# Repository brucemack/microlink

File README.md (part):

# Overview

Is it possible to build a full EchoLink&reg; node using a $6 microcontroller?  I'm not completely sure, but
let's find out. The goal of this project is to create the smallest, 
cheapest way to put a radio onto the EchoLink network. If you are new 
to the world of EchoLink please 
[see the official website](https://www.echolink.org/) for complete information. EchoLink is a 
peer-to-peer VoIP (voice over IP) network used to link amateur radio stations across
the Internet.

There are much easier ways to get onto EchoLink. The MicroLink project will only
be interesting to someone who wants to get deep into the nuts-and-bolts of EchoLink/VoIP technology. In fact, you 
should start to question the sanity of anyone who spends this much time building their own EchoLink station. I am a homebrew enthusiast and I try to avoid off-the-shelf software/components where 
possible. This has been a huge learning opportunity.

The system currently runs on a Pi Pico W (RP204, ARM Cortex M0) board. I'm pretty sure it 
could also run on an ESP-32, or possibly an Arduino of sufficient caliber. More experimentation
is needed here.

The software is fully open source. Now that EchoLink is "open," others can experiment with this 
important amateur radio technology. I am currently working on adding support for [AllStarLink](https://www.allstarlink.org/). More 
to follow ...

Here's my production setup at the moment. This station provides EchoLink access to the Wellesley Amateur 
Radio Society repeater (W1TKZ-L) using a Yaesu FT-1900:

The green case contains the MicroLink system. The DB9 connector on the side of the 
case connects to microphone and audio plugs on the FT-1900. A 12V supply powers the radio and the MicroLink interface.
Note that there are no other computers required.  The only
things not shown in this picture are the antenna (on the roof), and the home WIFI network that the Pico W is connected to.  The red LED is the 12V 
power indicator and the blue LED is the 
internet connection status.

Here's a demo video I made of the first bench test:

The microphone/analog section still needs some work. 

Here's what it sounds like over the air:

The official 
PC-based EchoLink client written by Jonathan Taylor (K1RFD) is excellent and is the quickest/easiest way to get on 
EchoLink. [Download it here](https://www.echolink.org/download.htm). There are also versions that run on mobile phones. MicroLink is not a supported part of the EchoLink family 
of products.

I've learned many things about EchoLink during this project. One thing is for sure: Jonathan (K1RFD) 
who created the EchoLink system is an outstanding engineer and we should all be greatly 
appreciative of the work
that he and the rest of the EchoLink team do on behalf of the amateur radio community. Thanks to 
Jonathan for his suggestions/advice along the way.

Huge thanks go to Steve Kondo (K1STK) for providing the mechanical design work
for this project.

Thanks also to Julius Jones (W2IHY), creator of the world-famous EQPlus and other sophisticated audio gear, for his
advice on the audio circuit.

I have a few extra boards which I would be willing to sell
for a reasonable price if someone wanted to try to build 
a station of their own.

I am [good in QRZ at KC1FSZ](https://www.qrz.com/db/kc1fsz) if you have any questions or suggestions.  Or e-mail at bruce at mackinnon dot com.

# Architecture Overview/Parts

My goal was to build a complete station from scratch, with no strings attached to PCs/servers.  

I have made a PCB for 
ease of use with radios (link mode) and/or direct integration with repeaters. Further refinements
of the PCB are in process. The [latest Gerbers are here](hw/ML4/plot/ML4.zip) and 
the [latest BOM is here](hw/ML4/ML4-bom.csv). You can build one yourself.

This project required an in-depth examination of how the EchoLink protocol works. [The notes
I created during this analysis are located here](https://github.com/brucemack/microlink/blob/main/docs/el_supplement.md). The reverse-engineering of the EchoLink protocol was the 
most time-consuming part of the project.

## Current Parts List (HW)

* The main processor is a Pi Pico W (RP2040) development board. This includes WIFI 
connectivity.  $6.00 on DigiKey. 
* A 4G cellular data option is available using a SIM7600 module. *(Not fully working yet.)*
* Audio output generation uses the MicroChip MCP4725 I2C digital-to-analog converter.  $1.27 on DigiKey.
* Audio input sampling uses the integrated ADC in the RP2040.
* Isolation transformers and optocouplers are used to eliminate the need for a common ground 
between the radio and the MicroLink system. The 
radio and the MicroLink circuitry are completely isolated from each other. This helps to reduce digital noise. 
* The radio link is an ~~AZDEN PCS-6000H~~ Yaesu FT-1900 mobile rig.
* When not using the radio:
  - Audio amplification uses the LM4862M 825mW amplifier.  $2.23 on DigiKey.
  - The local T/R key is from Federal Telephone and Telegraph Company (Buffalo, NY), made in 1920.  Priceless.
  - The microphone is an electret condenser with a LVM321 pre-amp and low-pass anti-aliasing 
filter.  The microphone part needs work. The next revision will use a TLV9161 op amp for the 
microphone pre-amp to reduce noise.

Here's a picture of the the current version of the PCB.  

This is a picture of the cellular module.  This has passed some initial tests, but is not ready for production yet.

## Current Parts List (SW)

* The main station firmware is completely homebrew (C++, see GitHub repo).
* The LwIP embedded TCP/IP stack is used for IP connectivity on the Pi Pico W.
* Importantly, audio compression/decompression uses a GSM 06-10 Full Rate CODEC which is homebrew 
in C++. Getting that to work required studying
the European Telecommunications Standards Institute specification for GSM and a lot of testing,
but this was extremely interesting.
* I'm not using the Arduino development environment for this project. The toolchain is 
CMake/GCC/GDB using the Pico W 
SDK. I like this environment a lot. The firmware is flashed via SWD using [openocd](https://openocd.org/).

MicroLink identifies itself using a version string of **0.02MLZ**.

## Analog Schematics

**Microphone Pre-Amp**

Performance audio circuits are not my forte.  The quality is improving with each 
iteration.  This is what I built originally, but a new version using parts with better noise 
specs is in the works. 

The microphone part will not be used when the radio is integrated. I will probably leave
the speaker/amplifier in for monitoring purposes.

**Audio Input**

This is the circuit used when connecting directly to a radio's AF output (i.e. no microphone). This repeats some of the circuit shown above (but minus the high gain). This also shows
the circuit used for carrier detect (COS). The idea is to boost up the rig's audio 
output (U6) and then compare it to an adjustable threshold (U8).  There is no debounce
in the analog part of the COS circuit - that is all done in software.

**Audio Output**

This is a work in process. The performance on the low end of the audio spectrum is not good yet.

## Cellular Data Interface

I have a working version of the MicroLink system using 4G cellular internet 
connectivity using an SIM7600A cellular module.  The $70 USD breakout 
board for this module [comes from Waveshare and is linked here](https://www.waveshare.com/sim7600a-h-4g-hat.htm).  
The Waveshare module was originally designed to plug into a full Raspberry Pi (NOT A PICO!), hence the 
use of the term "hat," but it is possible to use the module directly via a serial 
interface and there is no technical requirement to connect it to a Raspberry Pi.

I am communicating with the module using their AT command set across a 115,200 baud serial link.  This 
requires a pretty elaborate
state machine to allow bi-directional UDP traffic across a protocol that was originally designed
so support auto-dialing modems.  The Hayes people would be shocked if they saw what people were
doing with AT commands.  I've had good luck getting the SIM7600 to maintain the UDP data rate needed to
support EchoLink.

I am using a pre-paid SIM card from [Mint Mobile](https://www.mintmobile.com/).  It turns out that 
not all cellular providers support the "raw" SIM7600 module.  In fact, it took a few conversations
with their help desk to get them to activate my SIM card.  The Mint Mobile activation website wants you to select
what kind of phone you have (i.e. iPhone, Android, etc.) and apparently "homebrew EchoLink station"
isn't a valid choice in their system yet.  Someday ... But after some back-and-forth, they activated my 
SIM and within 30 seconds the "link" LED started flashing and I was on the Internet!

The only bad thing about Mint Mobile is that they don't appear to allow inbound UDP traffic 
into this module. Or at least I've not figured that out yet.  ARRGG! This required the use of a 
TCP proxy to handle the traffic in/out of the cellular module.  I've not documented this part
yet because I am still hoping to eliminate this component.

### Notes on MVNOs

Mint Mobile is an example of what is called a "Mobile Virtual Network Operator," or MVNO for short.
The real mobile cellular infrastructure is built/run by Verizon, T-Mobile (including the remnants of 
Sprint), AT&T, and US Cellular. 
All of the other low-cost "providers" are essentially renting bandwidth from the big firms. In the
case of Mint Mobile, they are using the T-Mobile network.

One interesting facet of the MVMO service is that the traffic is de-prioritized vs. the "real" 
carrier's traffic.  So during congested times you might find that T-Mobile service is 
better than Mint Mobile's.  You get what you pay for.

The mechanics of the prioritization is managed through the assignment of QCI levels.  According to one 
article I saw, T-Mobile uses QCI 6, 7, 8, and 9 for their normal consumer plans.   *The lower numbers 
have higher priority.* T-Mobile uses 6 (the best) for their "real" customers (i.e. pre-paid subscribers) and 7 for 
Mint Mobile.  Interestingly, T-Mobile branded hot-spots run on level 9 (the worst).

## Notes on SNTP

MicroLink will update its internal time using an NTP server.  The main value of this is to 
ensure that the timestamps on the internal log messages are correct.

The SNTP message protocol is quite simple.  The request is 68 bytes, mostly zeros.  The non-zero
bytes are as follows:

* Byte 0: (binary) 00 100 011.  This denotes an SNTPv4 client request.
* Byte 1: zero
* Byte 2: 6
* Byte 3: 0xec
* Bytes 12-15: (ascii) UKNO
* Bytes 40-43: The client's current time in seconds since the Epoch, big endian format.

The response that comes back has been observed to be around 52 bytes, although this may
vary in some situations.  The important information in the response is:

* Byte 0: (binary) 00 100 100.  This denotes an SNTPv4 server response.
* Bytes 40-43: The server's current time in seconds since the Epoch, big endian format.

## Enclosure

Steve K1STK designed and fabricated a great enclosure on his 3D printer.  Here's what the PCB
looks like with the case:

## Speeds and Feeds

* The standard audio sample rate for GSM-FR/EchoLink is 8 kHz at 12-bits of resolution.
* The audio CODEC creates/consumes one 640 byte packet every 80ms.  One of these packets is moved 12.5 times per second.
* It takes the RP2040 about 3ms to decode a 33 byte GSM frame into PCM.
* It takes the RP2040 about 7ms to encode a 160 sample PCM frame into GSM.
* The UDP data rate needed to sustain audio quality is 
approximately 14,000 baud.
* The RP2040 runs at 125 MHz. Only one of the two processors is used at this time.
* The DAC runs on an I2C bus running at 400 kHz.
* The voice prompts (all letters, numbers, and a few words) take up about 40K of 
flash. The audio is stored in GSM full-rate format for efficiency.
* Current flash size (used) is ~650,000 bytes.
* The RP2040 communicates with the SIM7600 4G cellular module at 115,200 baud.  This is 
about 10x the theoretically-required bandwidth to maintain a single channel.

# User Guide

## Serial Command Interface

(More detail to follow)

    reboot
    status 
    log
    tone
    dropall
    add [callsign]
    drop [callsign]

Configuration commands - using during initial setup:

    set addressingserver [EchoLink addressing server hostname: ex: naeast.echolink.org]
    set callsign [your call]
    set password [your password]
    set fullname "[your full name]"
    set location "[your location]"
    set wifissid "[yourssid]"
    set wifipassword [your password]
    set hardcos [0 or 1.  Enables or disables hardware carrier detect. Defaults to 0.]
    set coson [COS debounce ms during off->on transition. Defaults to 10.]
    set cosoff [COS debounce ms during on->off transition.  Defaults to 400.]
    set costhreshold [noise power floor used to decide when COS is detected]
    set adcoffset [value that is added to the raw ADC value.  Used to center the DC bais at 2048.]

## DB9 Connector Pinout

The MicroLink device provides a DB9 (female) connector with the following pinout:

Top row, left to right (looking into device connector)
* Pin 5: Audio out (rig microphone in)
* Pin 4: PTT out (rig PTT in).  This pin will be pulled to rig ground to key the rig.
* Pin 3: COS in (rig COS out). Pull to rig ground to indicate RX carrier. This is an optional connection and is only used when hardware carrier detect is available.
* Pin 2: NC
* Pin 1: Audio in (+) (rig speaker out)

Bottom row, left to right (looking into device connector)
* Pin 9: Rig Ground
* Pin 8: Rig Ground
* Pin 7: Rig Ground
* Pin 6: Audio in (-) (rig speaker out)

NOTES:
* Audio in (+) and audio in (-) are connected to the primary side of an audio isolation transformer.

# Technical/Development Notes

## GSM CODEC

I implemented my own fixed-point audio compression/decompression CODEC for the GSM 0610 Full Rate 
protocol [by following the specification here](https://www.etsi.org/deliver/etsi_en/300900_300999/300961/08.01.01_60/en_300961v080101p.pdf).  The coding scheme is the so-called **Regular Pulse Excitation - Long Term 
prediction - Linear Predictive Coder**, generally referred to as "RPE-LTP."  This standard was developed
as part of the modernization of the European mobile phone system in the late 1990s and is a good
balance between efficiency, quality, and compactness. 

The European Telecommunications Standards
Institute (ETSI) publishes a comprehensive set of test vectors containing known audio streams (PCM) and the 
corresponding GSM encoding. I have used that test data to validate that my CODEC is 100% complaint.

The smallest/cheapest microcontrollers lack hardware support for floating-point, so I built my CODEC using
fixed point (Q15) math. 

## Regarding Audio Smoothness

One of the most difficult challenges I had with this project was getting audio
that was "smooth" in both directions. This stuff is probably obvious to people
who are well versed in the state-of-the-art of VoIP.  Here
are a few points that will help anyone getting into this.

1. Accurate/consistent clocking of the audio chain is essential.  GSM uses
an 8 kHz clock, which means we need an audio sample once every
125 microseconds. I know this seems hard to believe, but inconsistencies
in this clock can be "heard."  This is where hardware timers with efficient
interrupt service architectures are important. The highest priority activity
of the microcontroller should be the creation/consumption of an audio sample
every 125 uS **exactly** - everything else in the system has some leeway.
2. An EchoLink receiver gets an audio packet _approximately_ every 80 ms.  Each 
packet contains
4 frames that each represent exactly 20 ms of audio. Finally, each frame contains 160
samples which each represent exactly 125 uS of audio.  From point #1 above, we already 
know that the timing of the 160 samples within each frame is critical.  However, 
we also need ensure that the 20 ms frames are played continuously 
**without the slightest gap between them.** This gets into an interesting problem
because the frames are streaming across the busy internet (not to mention 
low-cost WIFI hardware) and may be subject to 
small timing inconsistencies. There is simply no way to ensure that an EchoLink packet
will arrive every 80 ms. Sometimes the gap might be 81 ms, sometimes 79 ms, etc. 
This variability is known as "jitter" and it is a common issue in VoIP systems.
The fix is simple: we need to delay/buffer the audio generation in the receiver 
slightly to give ourselves a margin of error to accumulate packets. The
MicroLink system keeps a buffer of 16 audio packets and holds back the start 
of audio generation (after squelch break) until the buffer is half full.  This 
means that the receive path is delayed by around 8 x 80 ms *above and beyond* any delay
in the Internet itself. Experimental work is ongoing to make this adaptive
so that the delay is minimized.  Of course if the buffer empties out (i.e. several
slow packets in a row), all bets are off.
3. A MicroLink node can have up to four "remote" (i.e. internet based) stations
connected at the same time. Think of this as a mini-conference. In the extreme 
case (four users connected), the 
inbound audio packets from the station who is speaking need to be routed 
back out to the other three listening stations AND be sent to the CODEC/DAC for 
local radio transmission. Since the CODEC is relatively time-consuming, it is 
important to *reflect the audio packets back out onto the internet to the 
listening stations before dealing with the GSM decode needed for the local radio
link.* This will ensure maximum parallelism and smooth audio for all 
stations involved.

## Regarding the Pi Pico ADC

Two important things that make a difference for audio noise performance. Note
that these comments are relevant when using the Pi Pico board as-is. The 
rules will be different if using the RP2040 chip directly.

Per Pico datasheet:

> For much improved ADC performance, an external 3.0V shunt reference, such as LM4040, 
can be connected from the ADC_VREF pin to ground. Note that if doing this the ADC range 
is limited to 0-3.0V signals (rather than 0-3.3V), and the shunt reference will draw 
continuous current through the 200Ω filter resistor (3.3V-3.0V)/200 = ~1.5mA.

Per Pico datasheet:

> AGND is the ground reference for GPIO26-29, there is a separate analog ground plane 
running under these signals and terminating at this pin. If the ADC is not used or 
ADC performance is not critical, this pin can be connected to digital ground.

## Regarding Transmitter Duty Cycle

When using MicroLink as a bridge to a repeater system via a radio link, be careful about the 
duty cycle limitations of the bridge radio you are using.  The W1TKZ-L system uses an AZDEN mobile
rig that certainly wasn't designed for 100% key down.  

During "normal" repeater use this isn't a problem because the link radio is only keyed 
when a remote EchoLink user is speaking - that's no different from using the link
radio directly.  However, if more a complicated configuration is used (examples: linking 
two repeater systems together, joining a repeater to a conference server, etc.) things can become
problematic if the link radio is required to be keyed constantly to transmit the activity 
happening on the "other" repeater or in the conference.

If you have a transmitter than can be 
keyed for long periods of time then this won't be an issue. But if not, the MicroLink system supports a 
configurable duty cycle limit (defaults to 50%).  Once
the link radio has been keyed for more than 50% of the time in any 5 minute interval
the radio is un-keyed and allowed to rest. 

## Notes Regarding Interface with MCP4725

The RP2040 has no DAC and the MCP4725 is cheap and plentiful. This could certainly be 
done with a fancier audio CODEC, but we'll think about that later.

As mentioned previously, it is important to deliver audio very smoothly, and with 
as little CPU overhead as possible.  To that end, we are leveraging the TX FIFO 
on the I2C channel to quickly write to the I2C bus without any blocking.  

This is a bit tricky because there are two completely independent data formats
that need to work together:
* The RP2040 I2C format (really the DW_apb_i2c format) that is manifest in the 
format of the IC_DATA_CMD register.  Aside from the "normal" byte of data in this 
register, we have extra bits that control the START/STOP/RESTART cycles of the 
I2C bus.  Each write to the I2C_DATA_CMD register contributes both 
data bits and control bits.
* THe MCP4725 I2C format.  This is a 12-bit DAC, but it's not as simple as
justing writing 12 bits to it.  There are other control bits in the message
being sent to the MCP4725 on the I2C bus and those need to be configured
properly.

The DAC I2C writes are done inside of the same interrupt service routine that performs 
the ADC read. This interrupt is set to run at exactly 8kHZ by setting the ADC 
FIFO depth to 1. The ADC and DAC are both running constantly, regardless of whether
the system is transmitting or receiving.

### Bus Protocol

There are some different ways of using the I2C bus but we're using the 
simple way since speed is not a big issue.  What we really care about 
is consistency. Each audio sample will be transmitted
on the I2C bus using a normal START-address-data-STOP sequence. There are fancier 
things you can do on the I2C bus involving restarts but we don't need that
for our audio bandwidth requirements.  

The MCP4725 also provides some choices to improve efficiency.  The "fast mode" 
described in section 6.1.1 of [the datasheet](https://ww1.microchip.com/downloads/en/devicedoc/22039d.pdf) 
allows you to perform continuous data writes without addressing cycles. We don't 
need that for the 8kHz application (at least I don't think we do).

In the "slow" mode, the MCP4725 needs the regular I2C address byte followed
by three data bytes.  Actually, the first of the three data bytes is more 
like a command byte from the perspective of the MCP4725. So the complete
sequence will need to look like this:

* -> I2C START
* -> Address Byte (MCP4725 "first byte")
* <- I2C ACK
* -> Data Byte 0 (MCP4725 "second byte")
* <- I2C ACK
* -> Data Byte 1 (MCP4725 "third byte")
* <- I2C ACK
* -> Data Byte 2 (MCP4725 "fourth byte")
* <- I2C ACK
* -> I2C STOP

The START and STOP steps are commanded by bits in the RP2040 I2C_DATA_CMD word
so they don't require distinct writes to the TX FIFO. Likewise, the address
byte is generated automatically on start.  In order to achieve 
the sequence above we'll need to make three distinct data writes into the I2C
TX FIFO for each audio sample.

Combining the RP2040 datasheet figure 72 and the MCP4725 figure 6-2, we
can determine that the three writes will look like this:

    0 0 0 | 0   1   0   x   x   0   0   x 
    0 0 0 | d11 d10 d09 d08 d07 d06 d05 d04
    0 1 0 | d03 d02 d01 d00 x   x   x   x

These writes are happening into the LSB end of the I2C_DATA_CMD
register (i.e. data bits [10-0]).  Bits [31-11] are not used and
will be set to zero.  The x's in the illustration above show 
where the MCP4725 has don't-cares.  These will be set to zero.

## Notes on DTMF Detection

The rules for DTMF are standardize by the International Telecommunications Union (ITU). The relevant 
standards documents are located here:
* [ITU Q.23](https://www.itu.int/rec/dologin_pub.asp?id=T-REC-Q.23-198811-I!!PDF-E&lang=e&type=items)
* [ITU Q.24](https://www.itu.int/rec/dologin_pub.asp?lang=e&id=T-REC-Q.24-198811-I!!PDF-E&type=items)

The most important details from the standards document:

* There are a total of 16 possible symbols.  Each symbol is made up of two tones: one from the "low group"
and one from the "high group."
* The "low group" frequencies are: 697, 770, 852, 941 Hz.  These are on the rows of the keypad.
* The "high group" frequencies are: 1209, 1336, 1477, 1633 Hz.  These are on the columns of the keypad.
* Even though the phone/radio keypad only has 3 columns, there is a an "extra" column in the spec
for A/B/C/D.
* Transmission must be within 1.8% of frequency standard to be recognized.  This means that the received 
frequency can be +/- 1.8% from expectation, or 3.6% wide.  
* If we apply the 3.6% rule to the highest frequency, we get a resolution bandwidth of 58.788 Hz (1633 * 0.036).
* Distortion products (e.g. harmonics) must be -20dB below the fundamental.
* There are rules around the relative powers of the two tones that make up the symbol. In the US, 
the high group frequency power level may be up to 4 dB more or 8 dB less than the low group frequency 
power level for the symbol to be considered valid.  In the TELCO lingo, this difference is known as
"twist" and it is expressed in dB.  Positive twist means that the higher frequency is louder.
* Timing requirements are as follows.
  - A symbol must be transmitted for at least 40ms.  Symbols shorter than 23ms must be rejected.
  - The gap between symbols must be at least 40ms.

### Implementation Notes

* 23ms is 184 samples at a sampling rate of 8 kHz.  We will round this to 20ms (160 samples) since it 
is conveniently the same size as a GSM frame.
* 40ms is 320 samples at a sampling rate of 8 kHz
* A block of 136 samples is required to achieve 58.788 Hz resolution at a sampling rate of 8 kHz.  If
we use more than 136 samples then the resolution will become finer than 58 Hz and we'll need to compute
the power in more than one bucket - so we don't want to do that.
* So for each 160 sample frame we will use the latest 136 samples and ignore the other 24.  Close
enough.
* We will look for symbols that last more than two 160 sample frames.
* We will look for noise periods that last more than two 160 sample frames to consider the symbol valid
(i.e. the pause).
* Algorithm notes:
  - For each 160 samples.
  - Evaluate power at all 8 frequencies.
  - Compare the power of all 16 pairs by summing powers at each intersection.
  - Look to see if any pairs stand out by at least +20dB.  If so, that is the candidate pair.
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
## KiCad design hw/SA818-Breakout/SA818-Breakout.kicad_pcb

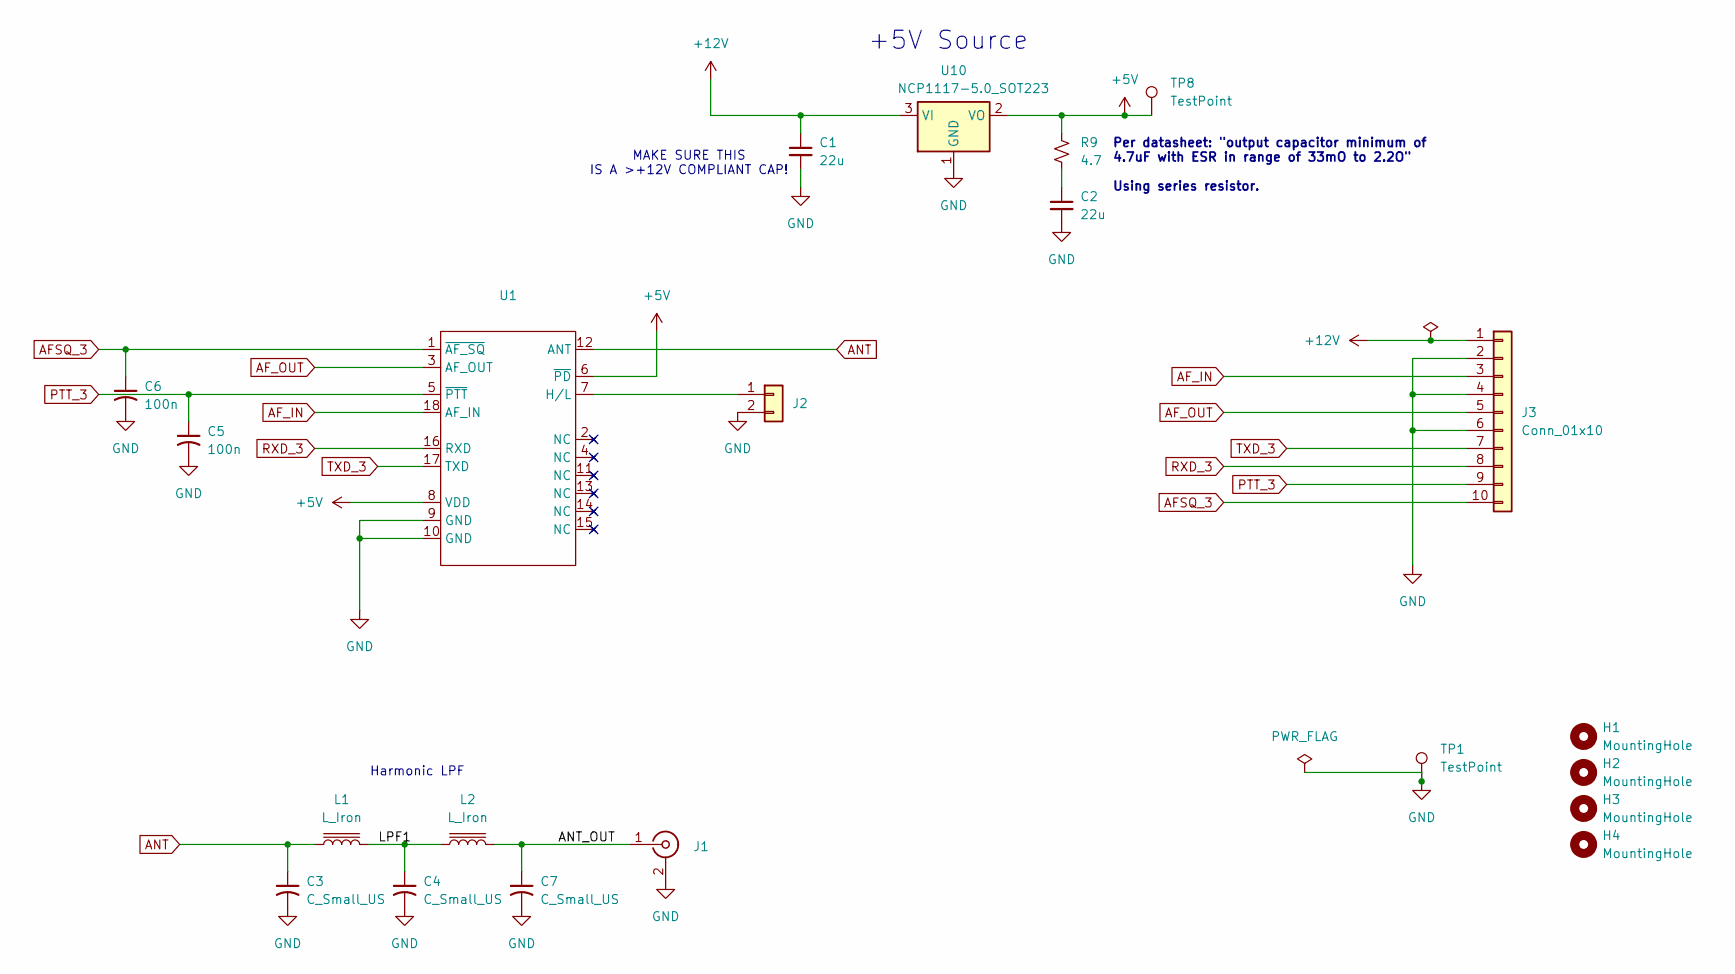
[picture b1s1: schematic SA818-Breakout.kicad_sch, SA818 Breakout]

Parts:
C1, C2: 22u; C_0805_2012Metric_Pad1.18x1.45mm_HandSolder
C3, C4, C7: C_Small_US; C_0805_2012Metric_Pad1.18x1.45mm_HandSolder
C5, C6: 100n; C_0805_2012Metric_Pad1.18x1.45mm_HandSolder
H1, H2, H3, H4: MountingHole; MountingHole_4mm
J1: Conn_Coaxial; SMA_Amphenol_901-144_Vertical
J2: Conn_01x02; PinHeader_1x02_P2.54mm_Vertical
J3: Conn_01x10; PinHeader_1x10_P2.54mm_Vertical
L1, L2: L_Iron; L_Axial_L6.6mm_D2.7mm_P10.16mm_Horizontal_Vishay_IM-2
R9: 4.7; R_0805_2012Metric_Pad1.20x1.40mm_HandSolder
TP1, TP8: TestPoint; TestPoint_Pad_2.5x2.5mm
U1: SA818
U10: NCP1117-5.0_SOT223; SOT-223-3_TabPin2

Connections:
+5V: R9.1, TP8.1, U1.6 (~PD), U1.8 (VDD), U10.2 (VO)
+12V: C1.1, J3.1, U10.3 (VI)
/ANT_OUT: C7.1, J1.1 (In), L2.2
/LPF1: C4.1, L1.2, L2.1
AFSQ_3: C6.1, J3.10, U1.1 (~AF_SQ)
AF_IN: J3.3, U1.18 (AF_IN)
AF_OUT: J3.5, U1.3 (AF_OUT)
ANT: C3.1, L1.1, U1.12 (ANT)
GND: C1.2, C2.2, C3.2, C4.2, C5.2, C6.2, C7.2, J1.2 (Ext), J2.2, J3.2, J3.4, J3.6, TP1.1, U1.9 (GND), U1.10 (GND), U10.1 (GND)
unnamed: C2.1, R9.2
unnamed: J2.1, U1.7 (H/L)
PTT_3: C5.1, J3.9, U1.5 (~PTT)
RXD_3: J3.8, U1.16 (RXD)
TXD_3: J3.7, U1.17 (TXD)

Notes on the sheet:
+5V Source
MAKE SURE THIS IS A >+12V COMPLIANT CAP!
Harmonic LPF
Per datasheet: "output capacitor minimum of 4.7uF with ESR in range of 33mO to 2.2O" Using series resistor.

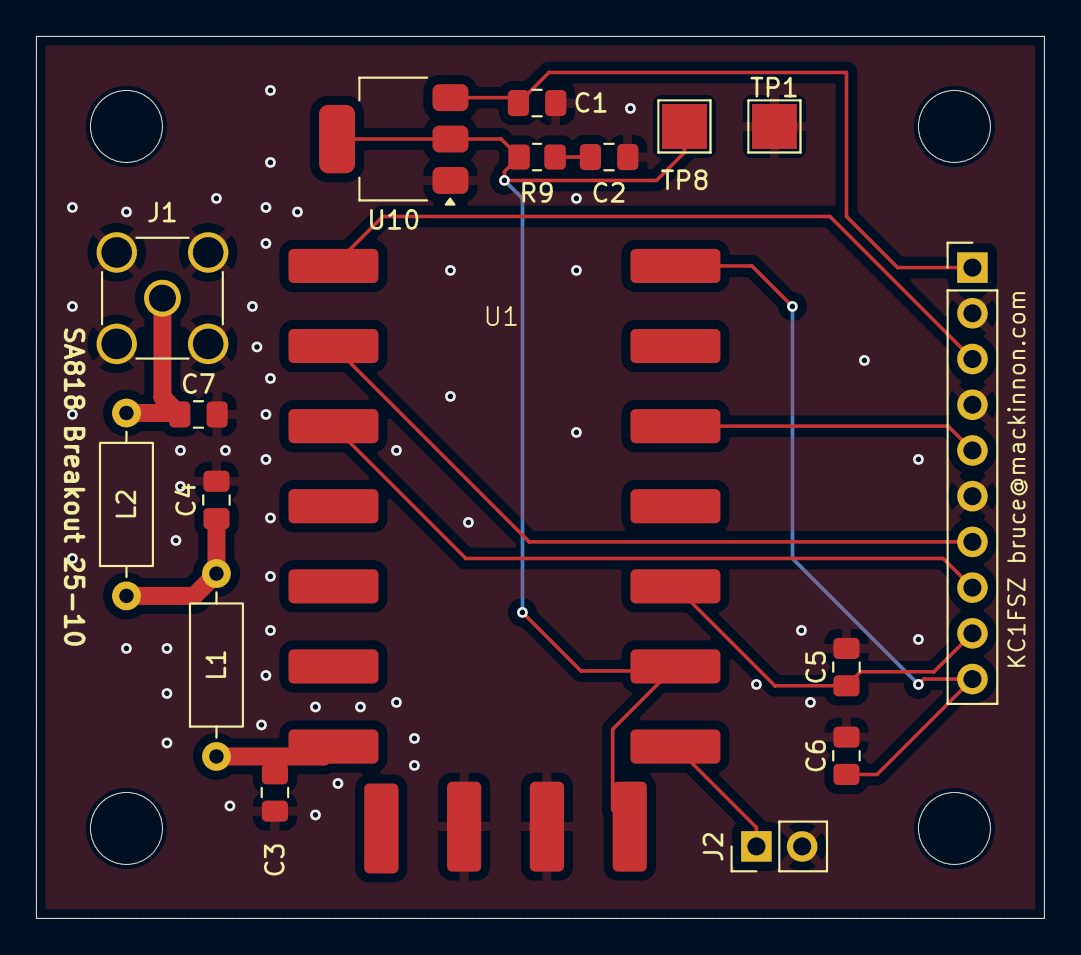
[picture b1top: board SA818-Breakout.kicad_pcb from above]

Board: 2 copper layers, 56.0 x 49.0 mm, 21 parts (0 on the bottom side), 14 nets.

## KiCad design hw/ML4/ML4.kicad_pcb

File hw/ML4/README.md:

This file contains the details for the version 3 (ML3) of the MicroLink hardware.
This is the first version that has a real enclosure so we are paying more attention
to mechanical detail.

# Enclosure Considerations
## Connectors That Penetrate the Enclosure
* DC power connector - 5.5mm jack, male center pin positive.
* Signal/audio connector - DB9, female.
## Indicators That Penetrate the Enclosure
* Three indicator LEDs - D1 Red, D3 blue, D4 green
## Thermal 
* The 3.3V LDO gets warm so there should be airflow in that vicinity

# Change Log (V3)

## R1 (17-Apr-2024)
* Moved Pi Pico W daughter card up by 1.00mm.
* Moved clear area under Pi Pico W daughter card up by 0.75mm.
* Moved J2 (5.5mm power jack) up by 2.5mm.
* Moved J1 (DB9) right by 2.5mm.

## During Build (25-Apr-2024)
* Changed R5 and R5 to 2.2K
* Changed R17, R20, R22 to 100 (LED)

DRC Notes:
* There are 12 warnings: "Silkscreen clipped by board edge."

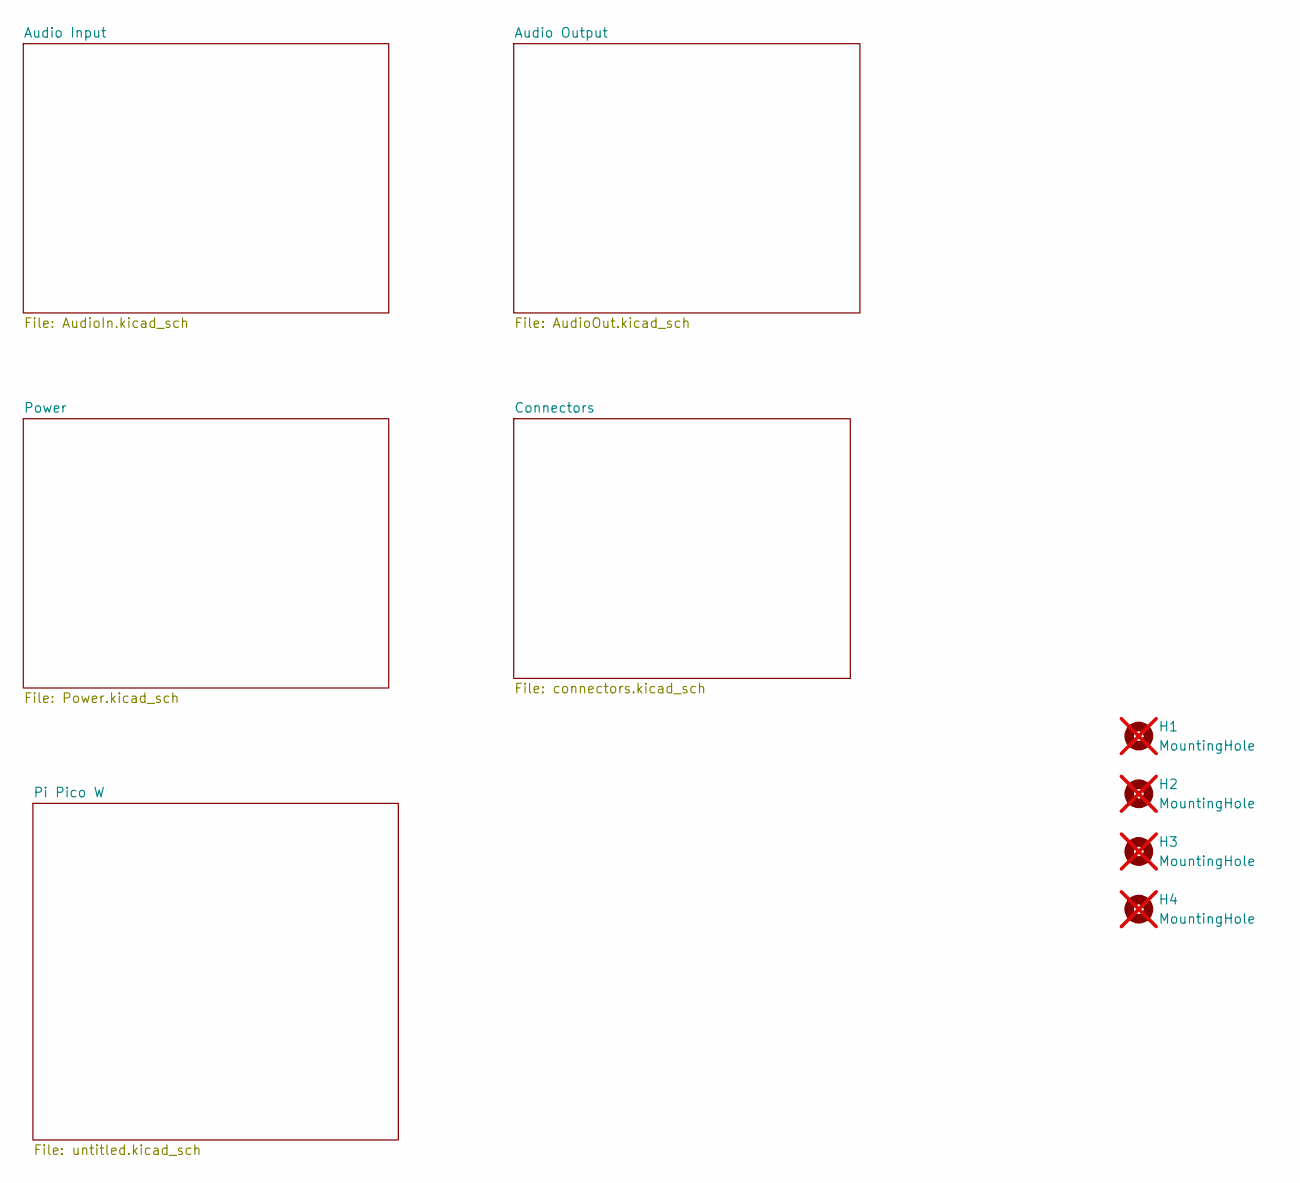
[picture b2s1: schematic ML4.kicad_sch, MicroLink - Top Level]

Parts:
H1, H2, H3, H4: MountingHole; MountingHole_4mm; not fitted

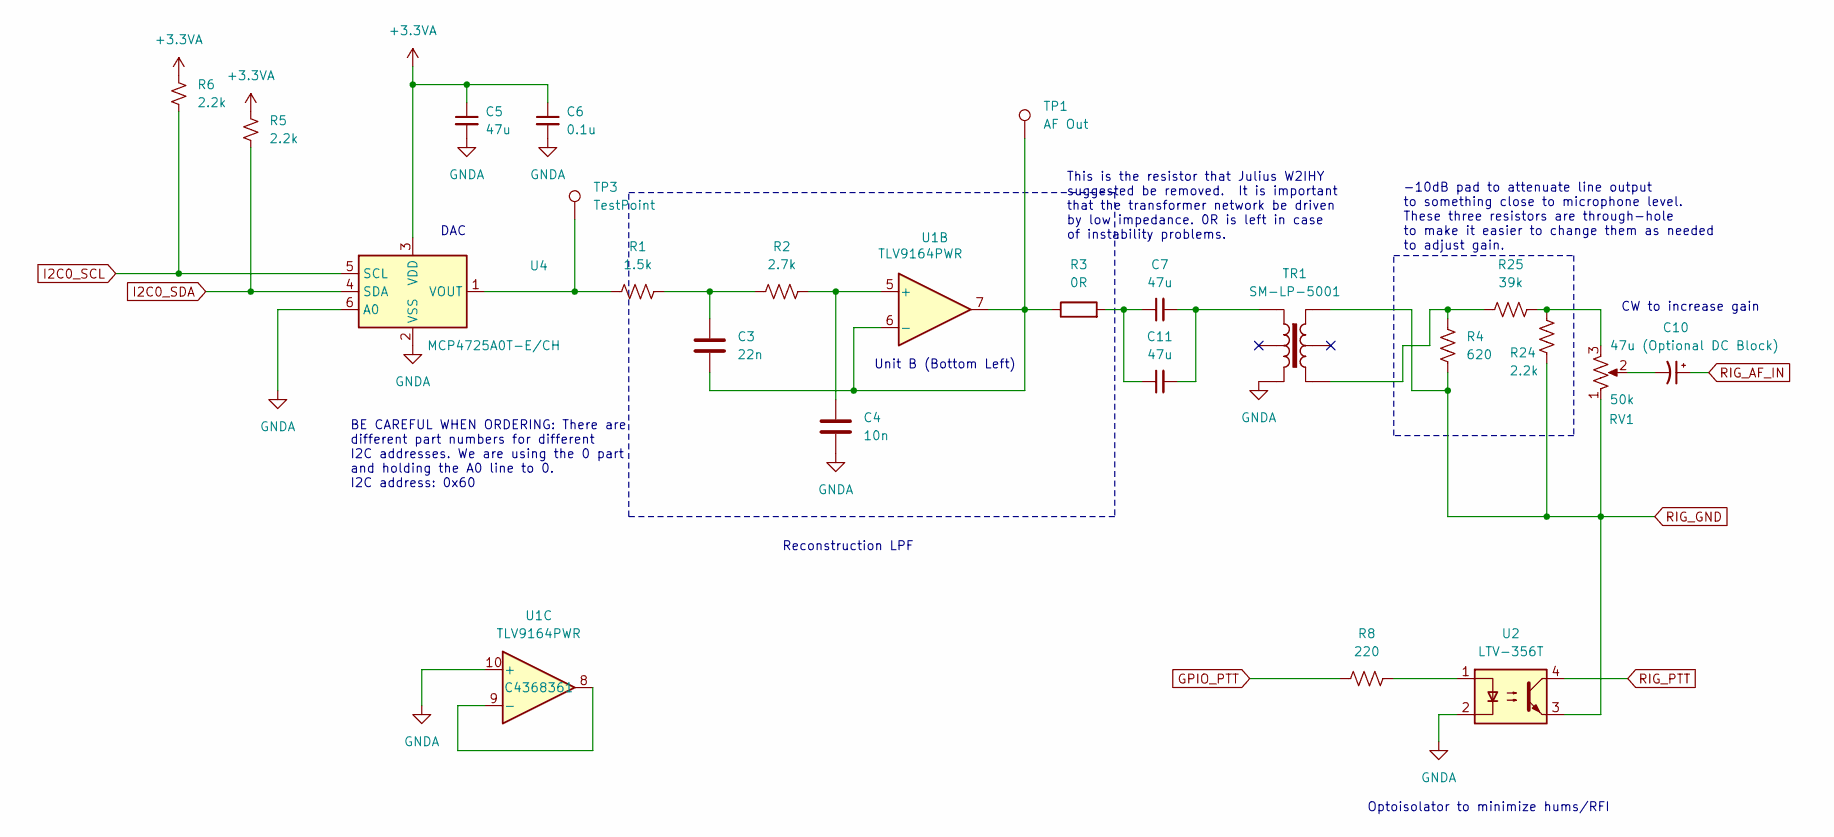
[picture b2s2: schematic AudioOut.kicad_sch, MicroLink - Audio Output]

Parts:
C3: 22n; C_0805_2012Metric_Pad1.18x1.45mm_HandSolder; LCSC C1729
C4: 10n; C_0805_2012Metric_Pad1.18x1.45mm_HandSolder; LCSC C1710
C5, C7, C11: 47u; C_0805_2012Metric_Pad1.18x1.45mm_HandSolder; LCSC C16780
C6: 0.1u; C_0805_2012Metric_Pad1.18x1.45mm_HandSolder; LCSC C28233
C10: 47u (Optional DC Block); CP_Radial_D5.0mm_P2.50mm; LCSC C22320
R1: 1.5k; R_0805_2012Metric_Pad1.20x1.40mm_HandSolder; LCSC C4310
R2: 2.7k; R_0805_2012Metric_Pad1.20x1.40mm_HandSolder; LCSC C17530
R3: 0R; R_1206_3216Metric_Pad1.30x1.75mm_HandSolder; LCSC C17477
R4: 620; R_Axial_DIN0309_L9.0mm_D3.2mm_P2.54mm_Vertical; LCSC C58633
R5, R6: 2.2k; R_0805_2012Metric_Pad1.20x1.40mm_HandSolder; LCSC C17520
R8: 220; R_0805_2012Metric_Pad1.20x1.40mm_HandSolder; LCSC C17557
R24: 2.2k; R_Axial_DIN0309_L9.0mm_D3.2mm_P2.54mm_Vertical; LCSC C58595
R25: 39k; R_Axial_DIN0309_L9.0mm_D3.2mm_P2.54mm_Vertical; LCSC C58645
RV1: 50k; POT_3362P; LCSC C81264
TP1: AF Out; TestPoint_Pad_2.5x2.5mm
TP3: TestPoint; TestPoint_Pad_2.5x2.5mm
TR1: SM-LP-5001; TRAN6_SM-LP-5001_BRN; LCSC C7503474
U1: TLV9164PWR; TSSOP-14_4.4x5mm_P0.65mm; LCSC C4368361
U2: LTV-356T; SO-4_4.4x3.6mm_P2.54mm; LCSC C125117
U4: MCP4725A0T-E/CH; SOT-23-6; LCSC C144198

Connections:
+3.3VA: C5.1, C6.1, R5.1, R6.1, U4.3 (VDD); also elsewhere on the board
GNDA: C4.2, C5.2, C6.2, TR1.3, U1.10 (+), U2.2, U4.2 (VSS), U4.6 (A0); also elsewhere on the board
GPIO_PTT: R8.1; also elsewhere on the board
I2C0_SCL: R6.2, U4.5 (SCL); also elsewhere on the board
I2C0_SDA: R5.2, U4.4 (SDA); also elsewhere on the board
unnamed: C3.1, R1.1, R2.1
unnamed: C10.2, RV1.2
unnamed: C7.1, C11.1, R3.2
unnamed: C7.2, C11.2, TR1.1
unnamed: R8.2, U2.1
unnamed: R24.2, R25.2, RV1.3
unnamed: R4.1, R25.1, TR1.4
unnamed: C4.1, R2.2, U1.5 (+)
unnamed: C3.2, R3.1, TP1.1, U1.6 (-), U1.7
unnamed: U1.8, U1.9 (-)
unnamed: R1.2, TP3.1, U4.1 (VOUT)
RIG_AF_IN: C10.1; also elsewhere on the board
RIG_GND: R4.2, R24.1, RV1.1, TR1.6, U2.3; also elsewhere on the board
RIG_PTT: U2.4; also elsewhere on the board

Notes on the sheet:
Reconstruction LPF
CW to increase gain
BE CAREFUL WHEN ORDERING: There are different part numbers for different I2C addresses. We are using the 0 part and holding the A0 line to 0. I2C address: 0x60
Optoisolator to minimize hums/RFI
-10dB pad to attenuate line output to something close to microphone level. These three resistors are through-hole to make it easier to change them as needed to adjust gain.
DAC
Unit B (Bottom Left)
This is the resistor that Julius W2IHY suggested be removed. It is important that the transformer network be driven by low impedance. 0R is left in case of instability problems.

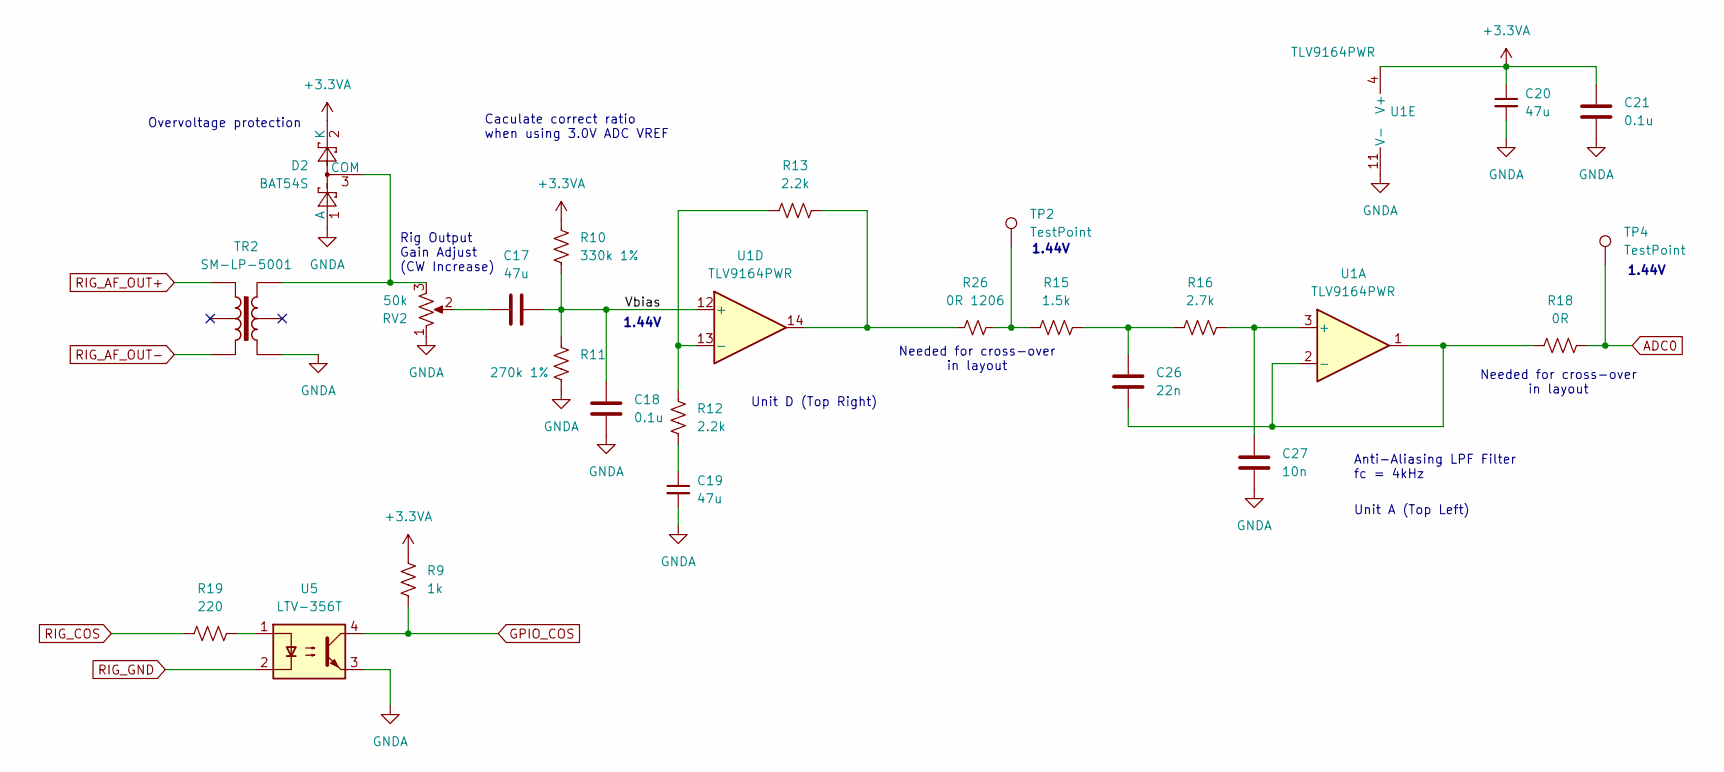
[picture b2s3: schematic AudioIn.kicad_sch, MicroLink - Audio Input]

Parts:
C17, C19, C20: 47u; C_0805_2012Metric_Pad1.18x1.45mm_HandSolder; LCSC C16780
C18, C21: 0.1u; C_0805_2012Metric_Pad1.18x1.45mm_HandSolder; LCSC C28233
C26: 22n; C_0805_2012Metric_Pad1.18x1.45mm_HandSolder; LCSC C1729
C27: 10n; C_0805_2012Metric_Pad1.18x1.45mm_HandSolder; LCSC C1710
D2: BAT54S; SOT-23; LCSC C12765
R9: 1k; R_0805_2012Metric_Pad1.20x1.40mm_HandSolder; LCSC C17513
R10: 330k 1%; R_0805_2012Metric_Pad1.20x1.40mm_HandSolder; LCSC C17629
R11: 270k 1%; R_0805_2012Metric_Pad1.20x1.40mm_HandSolder; LCSC C17589
R12, R13: 2.2k; R_0805_2012Metric_Pad1.20x1.40mm_HandSolder; LCSC C17520
R15: 1.5k; R_0805_2012Metric_Pad1.20x1.40mm_HandSolder; LCSC C4310
R16: 2.7k; R_0805_2012Metric_Pad1.20x1.40mm_HandSolder; LCSC C17530
R18: 0R; R_0805_2012Metric_Pad1.20x1.40mm_HandSolder; LCSC C17477
R19: 220; R_0805_2012Metric_Pad1.20x1.40mm_HandSolder; LCSC C17557
R26: 0R 1206; R_1206_3216Metric_Pad1.30x1.75mm_HandSolder; LCSC C17888
RV2: 50k; POT_3362P; LCSC C81264
TP2, TP4: TestPoint; TestPoint_Pad_2.5x2.5mm
TR2: SM-LP-5001; TRAN6_SM-LP-5001_BRN; LCSC C7503474
U1: TLV9164PWR; TSSOP-14_4.4x5mm_P0.65mm; LCSC C4368361
U5: LTV-356T; SO-4_4.4x3.6mm_P2.54mm; LCSC C125117

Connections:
+3.3VA: C20.1, C21.1, D2.2 (K), R9.1, R10.1, U1.4 (V+); also elsewhere on the board
/Audio Input/Vbias: C17.2, C18.1, R10.2, R11.1, U1.12 (+)
ADC0: R18.2, TP4.1; also elsewhere on the board
GNDA: C18.2, C19.2, C20.2, C21.2, C27.2, D2.1 (A), R11.2, RV2.1, TR2.4, U1.11 (V-), U5.3; also elsewhere on the board
GPIO_COS: R9.2, U5.4; also elsewhere on the board
unnamed: C17.1, RV2.2
unnamed: C19.1, R12.1
unnamed: C26.1, R15.1, R16.1
unnamed: D2.3 (COM), RV2.3, TR2.6
unnamed: R13.2, R26.1, U1.14
unnamed: R15.2, R26.2, TP2.1
unnamed: R19.2, U5.1
unnamed: C27.1, R16.2, U1.3 (+)
unnamed: C26.2, R18.1, U1.1, U1.2 (-)
unnamed: R12.2, R13.1, U1.13 (-)
RIG_AF_OUT+: TR2.1; also elsewhere on the board
RIG_AF_OUT-: TR2.3; also elsewhere on the board
RIG_COS: R19.1; also elsewhere on the board
RIG_GND: U5.2; also elsewhere on the board

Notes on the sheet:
Rig Output Gain Adjust (CW Increase)
Overvoltage protection
Unit D (Top Right)
1.44V
Unit A (Top Left)
Needed for cross-over in layout
Anti-Aliasing LPF Filter fc = 4kHz
Caculate correct ratio when using 3.0V ADC VREF

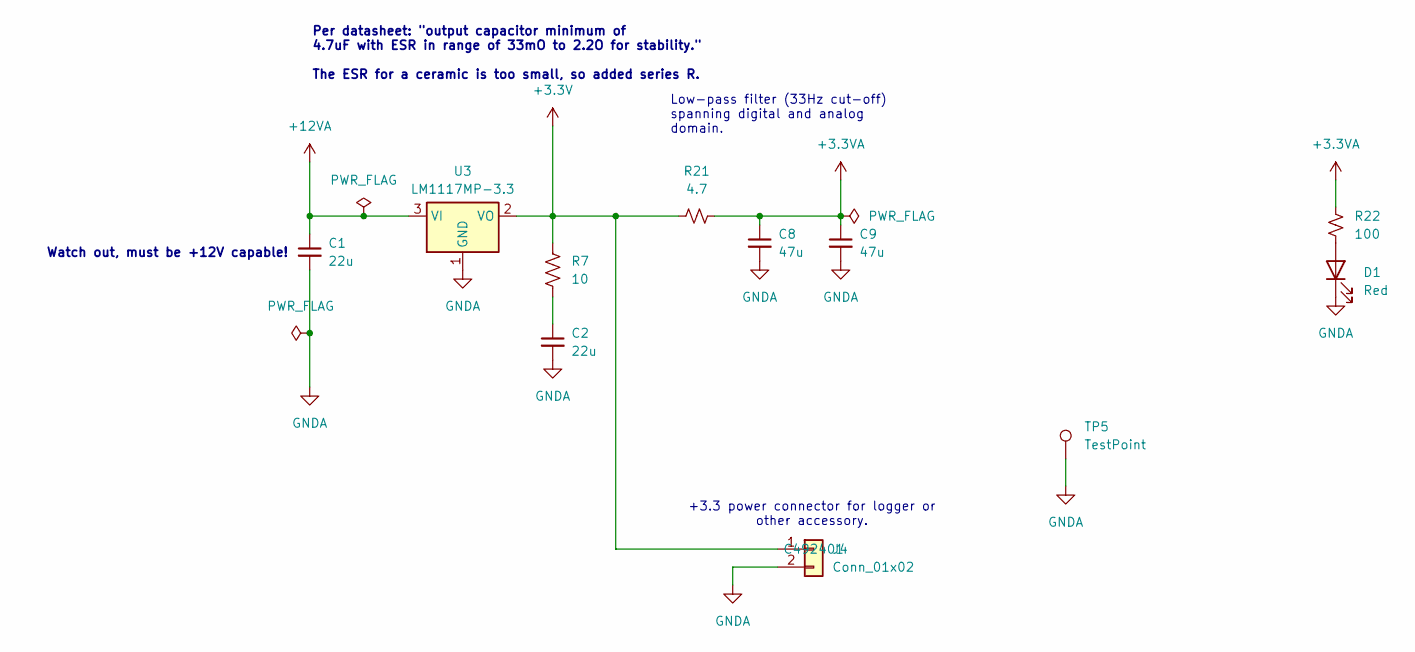
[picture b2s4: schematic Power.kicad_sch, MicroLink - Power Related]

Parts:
C1, C2: 22u; C_0805_2012Metric_Pad1.18x1.45mm_HandSolder; LCSC C45783
C8, C9: 47u; C_0805_2012Metric_Pad1.18x1.45mm_HandSolder; LCSC C16780
D1: Red; LED_0805_2012Metric_Pad1.15x1.40mm_HandSolder; LCSC C84256
J4: Conn_01x02; PinHeader_1x02_P2.54mm_Vertical; LCSC C492401
R7: 10; R_0805_2012Metric_Pad1.20x1.40mm_HandSolder; LCSC C17415
R21: 4.7; R_0805_2012Metric_Pad1.20x1.40mm_HandSolder; LCSC C17675
R22: 100; R_0805_2012Metric_Pad1.20x1.40mm_HandSolder; LCSC C17408
TP5: TestPoint; TestPoint_Pad_2.5x2.5mm
U3: LM1117MP-3.3; SOT-223-3_TabPin2; LCSC C9662

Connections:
+3.3V: J4.1, R7.1, R21.1, U3.2 (VO); also elsewhere on the board
+3.3VA: C8.1, C9.1, R21.2, R22.1; also elsewhere on the board
+12VA: C1.1, U3.3 (VI); also elsewhere on the board
GNDA: C1.2, C2.2, C8.2, C9.2, D1.1 (K), J4.2, TP5.1, U3.1 (GND); also elsewhere on the board
unnamed: C2.1, R7.2
unnamed: D1.2 (A), R22.2

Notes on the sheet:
+3.3 power connector for logger or other accessory.
Watch out, must be +12V capable!
Low-pass filter (33Hz cut-off) spanning digital and analog domain.
Per datasheet: "output capacitor minimum of 4.7uF with ESR in range of 33mO to 2.2O for stability." The ESR for a ceramic is too small, so added series R.

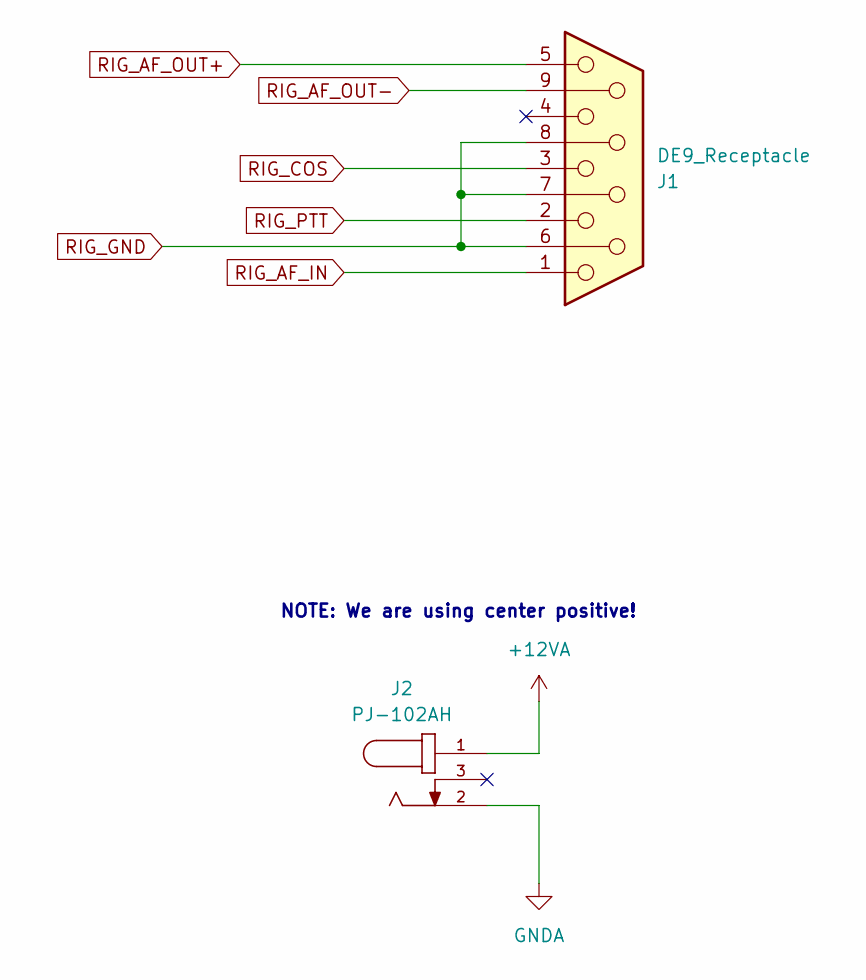
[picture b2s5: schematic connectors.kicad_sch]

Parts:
J1: DE9_Receptacle; CONN_A-DF 09 A&slash_KG-T2S_ASM; LCSC C17515865
J2: PJ-102AH; Power_5.5mm_CUI_PJ-102AH; LCSC C3096093

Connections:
+12VA: J2.1; also elsewhere on the board
GNDA: J2.2; also elsewhere on the board
RIG_AF_IN: J1.1; also elsewhere on the board
RIG_AF_OUT+: J1.5; also elsewhere on the board
RIG_AF_OUT-: J1.9; also elsewhere on the board
RIG_COS: J1.3; also elsewhere on the board
RIG_GND: J1.6, J1.7, J1.8; also elsewhere on the board
RIG_PTT: J1.2; also elsewhere on the board

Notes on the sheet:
NOTE: We are using center positive!

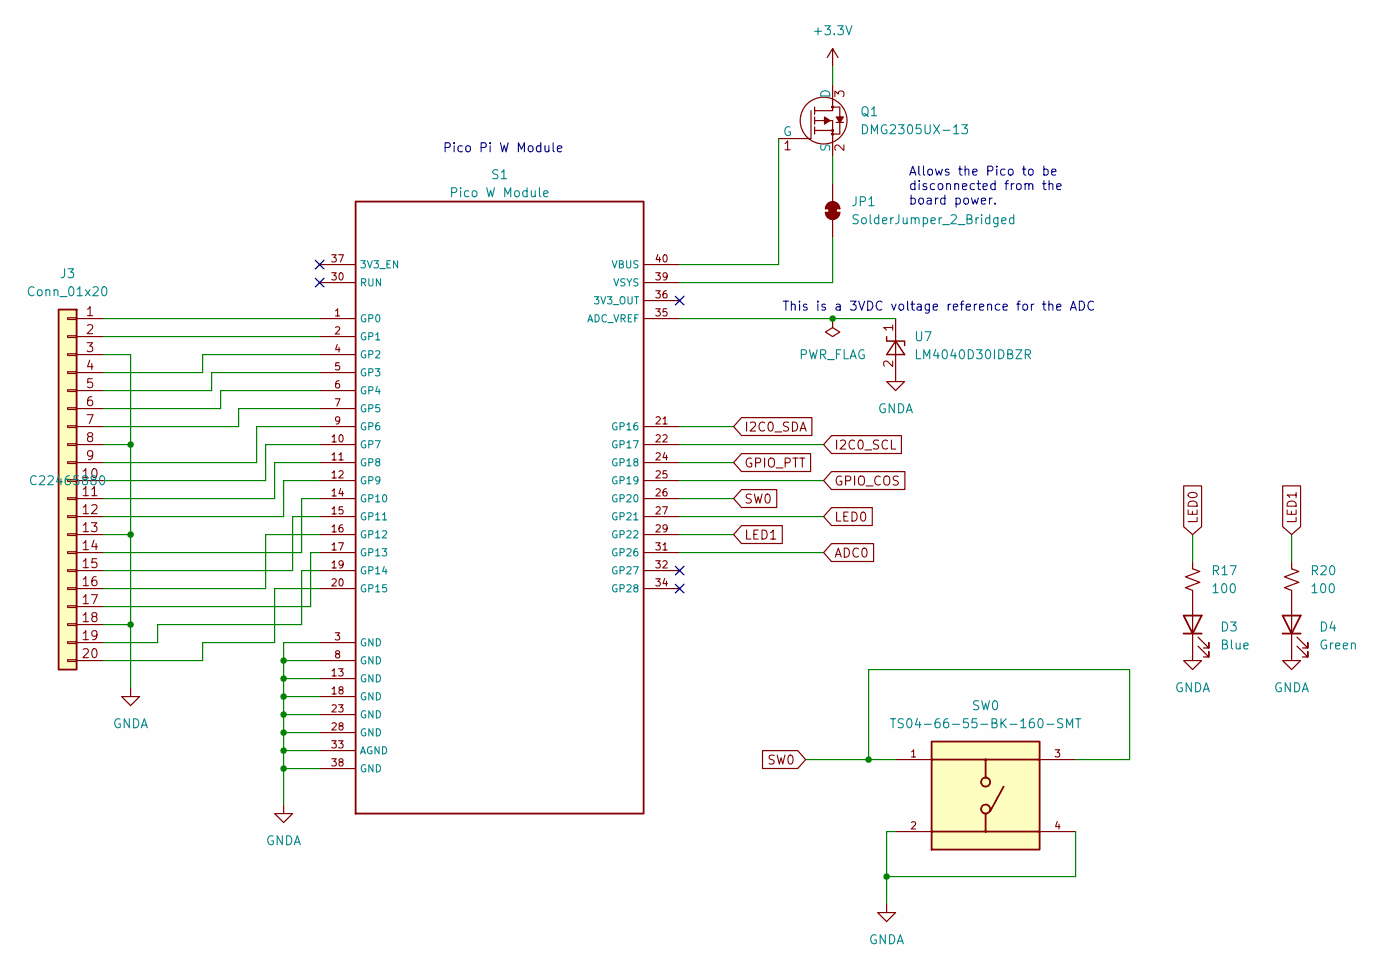
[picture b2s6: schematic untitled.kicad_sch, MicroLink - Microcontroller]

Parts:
D3: Blue; LED_0805_2012Metric_Pad1.15x1.40mm_HandSolder; LCSC C84259
D4: Green; LED_0805_2012Metric_Pad1.15x1.40mm_HandSolder; LCSC C2297
J3: Conn_01x20; PinHeader_1x20_P2.54mm_Vertical; LCSC C22465880
JP1: SolderJumper_2_Bridged; SolderJumper-2_P1.3mm_Bridged_Pad1.0x1.5mm
Q1: DMG2305UX-13; SOT-23_Handsoldering; MPN DMG2305UX-13; Digi-Key_PN DMG2305UX-13DICT-ND
R17, R20: 100; R_0805_2012Metric_Pad1.20x1.40mm_HandSolder; LCSC C17408
S1: Pico W Module; RPi_PicoW_SMD_TH; LCSC C7203003
SW0: TS04-66-55-BK-160-SMT; SW_TS04-66-55-BK-160-SMT; PARTREV 1.0; LCSC C4364775
U7: LM4040D30IDBZR; SOT-23; LCSC C2157213

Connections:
+3.3V: Q1.3 (D); also elsewhere on the board
ADC0: S1.31 (GP26); also elsewhere on the board
GNDA: D3.1 (K), D4.1 (K), J3.3, J3.8, J3.13, J3.18, S1.3 (GND), S1.8 (GND), S1.13 (GND), S1.18 (GND), S1.23 (GND), S1.28 (GND), S1.33 (AGND), S1.38 (GND), SW0.2, SW0.4, U7.2 (A); also elsewhere on the board
GPIO_COS: S1.25 (GP19); also elsewhere on the board
GPIO_PTT: S1.24 (GP18); also elsewhere on the board
I2C0_SCL: S1.22 (GP17); also elsewhere on the board
I2C0_SDA: S1.21 (GP16); also elsewhere on the board
LED0: R17.1, S1.27 (GP21)
LED1: R20.1, S1.29 (GP22)
unnamed: D3.2 (A), R17.2
unnamed: D4.2 (A), R20.2
unnamed: J3.1, S1.1 (GP0)
unnamed: J3.2, S1.2 (GP1)
unnamed: J3.4, S1.4 (GP2)
unnamed: J3.5, S1.5 (GP3)
unnamed: J3.6, S1.6 (GP4)
unnamed: J3.7, S1.7 (GP5)
unnamed: J3.9, S1.9 (GP6)
unnamed: J3.10, S1.10 (GP7)
unnamed: J3.11, S1.11 (GP8)
unnamed: J3.12, S1.12 (GP9)
unnamed: J3.14, S1.14 (GP10)
unnamed: J3.15, S1.15 (GP11)
unnamed: J3.16, S1.16 (GP12)
unnamed: J3.17, S1.17 (GP13)
unnamed: J3.19, S1.19 (GP14)
unnamed: J3.20, S1.20 (GP15)
unnamed: JP1.1 (A), S1.39 (VSYS)
unnamed: JP1.2 (B), Q1.2 (S)
unnamed: Q1.1 (G), S1.40 (VBUS)
unnamed: S1.35 (ADC_VREF), U7.1 (K)
SW0: S1.26 (GP20), SW0.1, SW0.3

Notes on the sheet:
This is a 3VDC voltage reference for the ADC
Allows the Pico to be disconnected from the board power.
Pico Pi W Module

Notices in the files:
src/link-main.cpp:
Copyright (C) 2024, Bruce MacKinnon KC1FSZ
This program is free software: you can redistribute it and/or modify
it under the terms of the GNU General Public License as published by
the Free Software Foundation, either version 3 of the License, or
(at your option) any later version.
hw/ML0/AudioIn.kicad_sch:
Copyright (C) 2024 - Not For Commercial Use
hw/ML4/AudioIn.kicad_sch:
Copyright (C) 2025 - Not For Commercial Use
